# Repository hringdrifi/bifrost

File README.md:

# Bifrǫst

Bifrǫst is a split-keyboard design project by [hringdrifi](https://github.com/hringdrifi).

It is a wireless keyboard design based on the MDBT50Q module, which uses the Nordic nRF52840 SoC.

## Project status

This keyboard is currently under active design. It is not yet a validated or production-ready design.

The case CAD files and PCB design files are published here. The keyboard firmware is maintained in the [zmk-config-bifrost repository](https://github.com/hringdrifi/zmk-config-bifrost).

## Available files

- [`case/`](case/README.md) — STEP files for the cases and switch plates
- [`pcb/`](pcb/) — KiCad sources for the five PCBs
- [`docs/manufacturing.md`](docs/manufacturing.md) — manufacturing reference ([日本語](docs/manufacturing.ja.md))
- [Firmware](https://github.com/hringdrifi/zmk-config-bifrost) — ZMK configuration and firmware source

## License

The design data in `case/` and `pcb/` is licensed under the [CERN Open Hardware Licence Version 2 - Permissive (CERN-OHL-P-2.0)](LICENSE).

This license permits use, modification, manufacture, and sale of the design data and products made from it. Modified design data does not need to be published, but applicable notices must be retained and modifications must be documented. The design data and any resulting products are provided without warranty.

The CERN-OHL-P-2.0 license applies to the contents of `case/` and `pcb/`. Firmware is licensed under the [MIT License](https://spdx.org/licenses/MIT.html).

## Disclaimer

Verify dimensions, clearances, compatibility, manufacturability, and safety for your own build before making any parts. Use of these files is at your own risk.

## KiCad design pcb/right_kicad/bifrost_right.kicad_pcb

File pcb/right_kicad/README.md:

# Bifrǫst right KiCad design

KiCad source files for the right half of Bifrǫst.

## Status

This is an **incomplete and unverified work in progress**. Do not order boards or rely on this design without independently reviewing the schematic, layout, footprints, mechanical fit, and electrical connections.

The project was initially created from a Smiðr export, then received substantial additional modifications. It is no longer an unmodified Smiðr export.

## Contents

| Design | Purpose |
| --- | --- |
| `bifrost_right.kicad_pro` / `.kicad_sch` / `.kicad_pcb` | Right main PCB |
| `bifrost_right_plate.kicad_pro` / `.kicad_pcb` | Right main switch plate |
| `bifrost_right_thumb.kicad_pro` / `.kicad_sch` / `.kicad_pcb` | Right thumb-cluster PCB |
| `bifrost_right_thumb_plate.kicad_pro` / `.kicad_pcb` | Right thumb-cluster switch plate |
| `bifrost_right_trackball.kicad_pro` / `.kicad_sch` / `.kicad_pcb` | Trackball PCB |
| `smidr.pretty/` | Project footprint library |
| `local.kicad_sym` | Project symbol library |

## Electrical design note

The switch design uses **direct GPIO connections**. Each switch is connected directly between its assigned GPIO net and GND; **there is no diode connected to each switch**.

## Libraries

`fp-lib-table` and `sym-lib-table` configure the project libraries. Keep `smidr.pretty/` and `local.kicad_sym` with this project when opening it in KiCad.

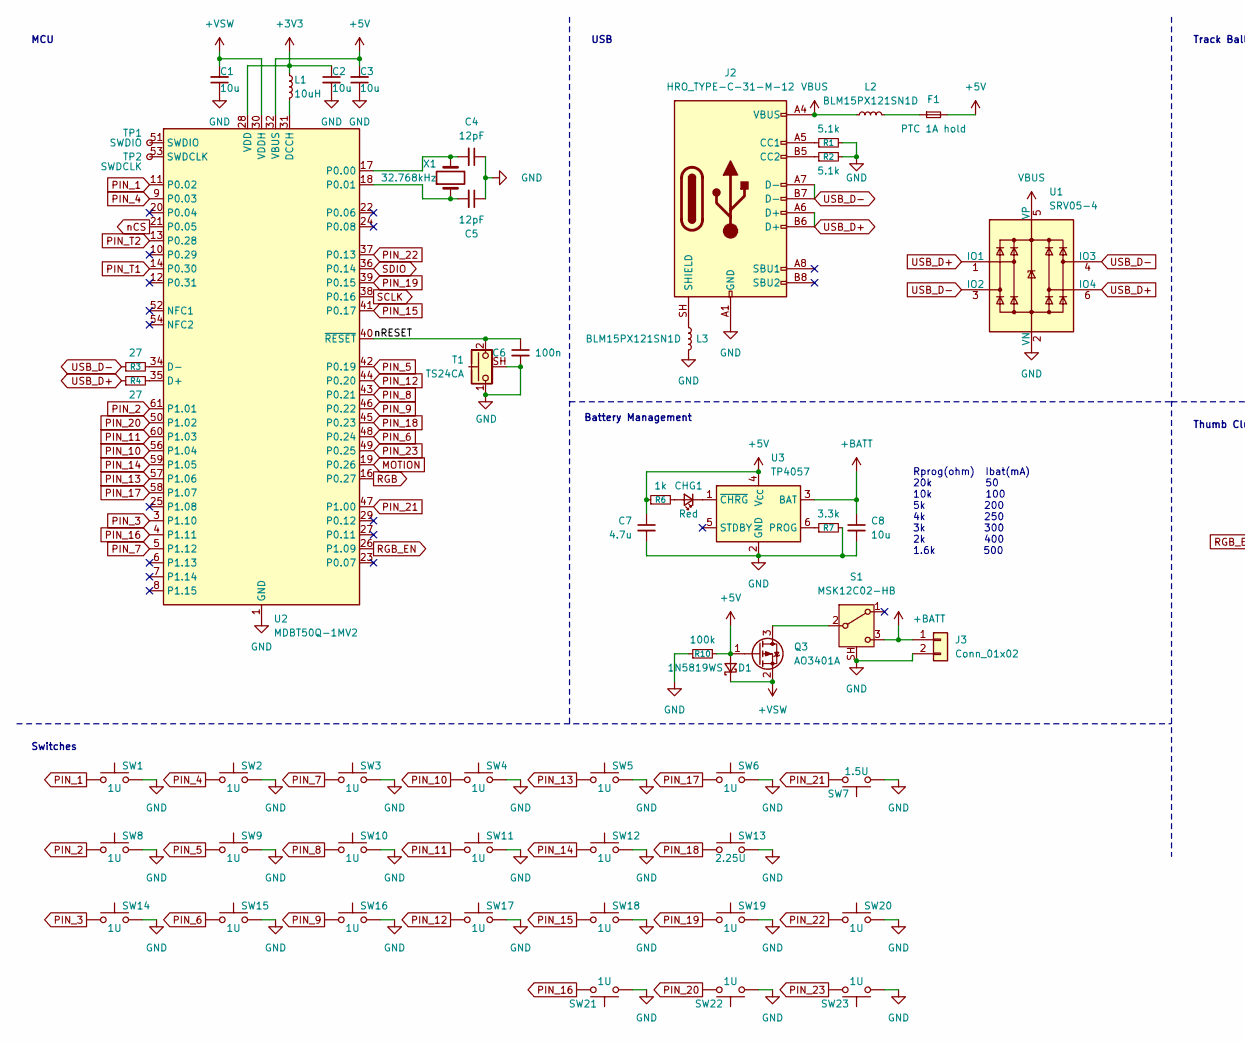
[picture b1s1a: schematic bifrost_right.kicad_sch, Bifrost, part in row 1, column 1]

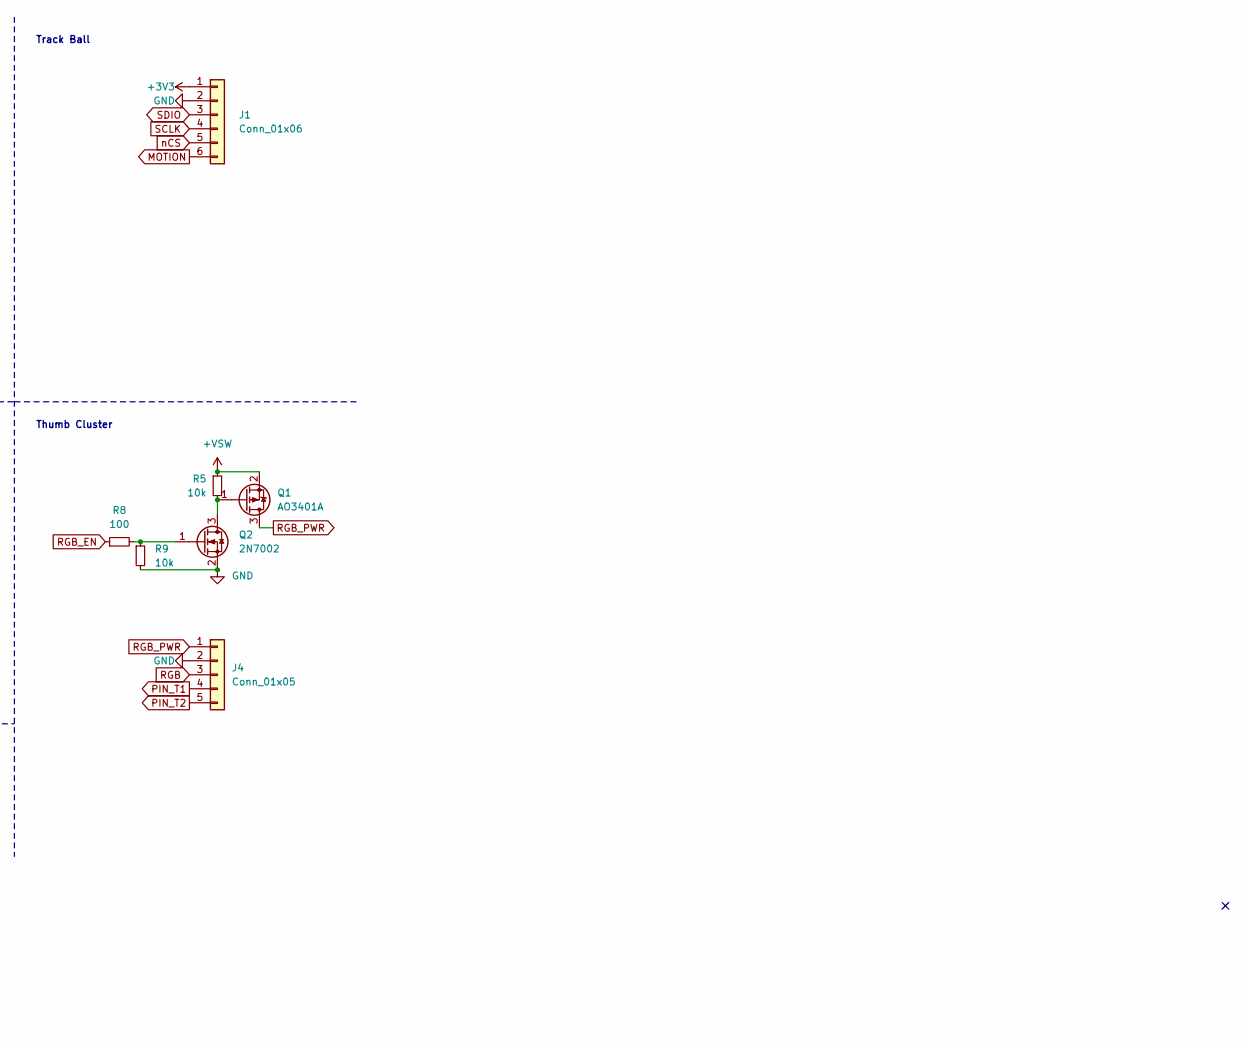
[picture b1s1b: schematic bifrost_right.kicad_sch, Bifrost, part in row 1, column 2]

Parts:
C1, C2, C3, C8: 10u; C_0402_1005Metric; JLCPCB Part # C15525
C4, C5: 12pF; C_0402_1005Metric; JLCPCB Part # C1547
C6: 100n; C_0402_1005Metric; JLCPCB Part # C1525
C7: 4.7u; C_0402_1005Metric; JLCPCB Part # C23733
CHG1: Red; LED_0603_1608Metric; JLCPCB Part # C19189741
D1: 1N5819WS; D_SOD-323; JLCPCB Part # C191023
F1: PTC 1A hold; Fuse_1206_3216Metric; JLCPCB Part # C883131
J1: Conn_01x06; PinHeader_1x06_P1.27mm_Vertical
J2: HRO_TYPE-C-31-M-12; USB_C_Receptacle_HRO_TYPE-C-31-M-12; JLCPCB Part # C165948
J3: Conn_01x02; PinHeader_1x02_P1.27mm_Vertical
J4: Conn_01x05; PinHeader_1x05_P1.27mm_Vertical
L1: 10uH; L_0603_1608Metric; JLCPCB Part # C86083
L2, L3: BLM15PX121SN1D; L_0402_1005Metric; JLCPCB Part # C88970
Q1, Q3: AO3401A; SOT-23; JLCPCB Part # C15127
Q2: 2N7002; SOT-23; JLCPCB Part # C8545
R1, R2: 5.1k; R_0402_1005Metric; JLCPCB Part # C25905
R3, R4: 27; R_0402_1005Metric; JLCPCB Part # C25100
R5, R9: 10k; R_0402_1005Metric; JLCPCB Part # C25744
R6: 1k; R_0402_1005Metric; JLCPCB Part # C11702
R7: 3.3k; R_0402_1005Metric; JLCPCB Part # C25890
R8: 100; R_0402_1005Metric; JLCPCB Part # C25076
R10: 100k; R_0402_1005Metric; JLCPCB Part # C25741
S1: MSK12C02-HB; SW_SPDT_Shouhan_MSK12C02; JLCPCB Part # C431541
SW1, SW2, SW3, SW4, SW5, SW6, SW8, SW9, SW10, SW11, SW12, SW14, SW15, SW16, SW17, SW18, SW19, SW20, SW21, SW22, SW23: 1U; SW_Smidr_Gateron_LP_Hotswap
SW7: 1.5U; SW_Smidr_Gateron_LP_Hotswap
SW13: 2.25U; SW_Smidr_Gateron_LP_Hotswap
T1: TS24CA; SW_SMD_2P-TS24CA; JLCPCB Part # C393942
TP1: SWDIO; TestPoint_THTPad_D1.0mm_Drill0.5mm
TP2: SWDCLK; TestPoint_THTPad_D1.0mm_Drill0.5mm
U1: SRV05-4; SOT-23-6; JLCPCB Part # C7420376
U2: MDBT50Q-1MV2; Raytac_MDBT50Q; JLCPCB Part # C5118826
U3: TP4057; SOT-23-6; JLCPCB Part # C12044
X1: 32.768kHz; Crystal_SMD_MicroCrystal_CC7V-T1A-2Pin_3.2x1.5mm; JLCPCB Part # C479190

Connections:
+3V3: C2.1, J1.1, L1.1, U2.28 (VDD)
+5V: C3.2, C7.1, D1.2 (A), F1.2, Q3.1 (G), R6.1, R10.2, U2.32 (VBUS), U3.4 (V_{CC})
+BATT: C8.1, J3.1, S1.3 (C), U3.3 (BAT)
+VSW: C1.2, D1.1 (K), Q1.2 (S), Q3.2 (S), R5.1, U2.30 (VDDH)
/nRESET: C6.1, T1.2, U2.40 (~RESET)
GND: C1.1, C2.2, C3.1, C4.1, C5.1, C6.2, C7.2, C8.2, J1.2, J2.A1 (GND), J2.A12 (GND), J2.B1 (GND), J2.B12 (GND), J3.2, J4.2, L3.2, Q2.2 (S), R1.2, R2.2, R7.2, R9.2, R10.1, S1.SH, SW1.2, SW2.2, SW3.2, SW4.2, SW5.2, SW6.2, SW7.1, SW8.2, SW9.2, SW10.2, SW11.2, SW12.2, SW13.2, SW14.2, SW15.2, SW16.2, SW17.2, SW18.2, SW19.2, SW20.2, SW21.1, SW22.1, SW23.1, T1.1, T1.SH (B), U1.2 (VN), U2.1 (GND), U2.2 (GND), U2.15 (GND), U2.33 (GND), U2.55 (GND), U3.2 (GND)
MOTION: J1.6, U2.19 (P0.26)
unnamed: CHG1.2 (A), R6.2
unnamed: CHG1.1 (K), U3.1 (~CHRG)
unnamed: F1.1, L2.2
unnamed: J2.A5 (CC1), R1.1
unnamed: J2.B5 (CC2), R2.1
unnamed: J2.SH (SHIELD), L3.1
unnamed: Q1.1 (G), Q2.3 (D), R5.2
unnamed: Q2.1 (G), R8.2, R9.1
unnamed: Q3.3 (D), S1.2 (B)
unnamed: R4.2, U2.35 (D+)
unnamed: R3.2, U2.34 (D-)
unnamed: L1.2, U2.31 (DCCH)
unnamed: C4.2, U2.17 (P0.00), X1.2
unnamed: C5.2, U2.18 (P0.01), X1.1
unnamed: TP2.1 (1_1), U2.53 (SWDCLK)
unnamed: TP1.1 (1_1), U2.51 (SWDIO)
unnamed: R7.1, U3.6 (PROG)
PIN_1: SW1.1, U2.11 (P0.02)
PIN_2: SW8.1, U2.61 (P1.01)
PIN_3: SW14.1, U2.3 (P1.10)
PIN_4: SW2.1, U2.9 (P0.03)
PIN_5: SW9.1, U2.42 (P0.19)
PIN_6: SW15.1, U2.48 (P0.24)
PIN_7: SW3.1, U2.5 (P1.12)
PIN_8: SW10.1, U2.43 (P0.21)
PIN_9: SW16.1, U2.46 (P0.22)
PIN_10: SW4.1, U2.56 (P1.04)
PIN_11: SW11.1, U2.60 (P1.03)
PIN_12: SW17.1, U2.44 (P0.20)
PIN_13: SW5.1, U2.57 (P1.06)
PIN_14: SW12.1, U2.59 (P1.05)
PIN_15: SW18.1, U2.41 (P0.17)
PIN_16: SW21.2, U2.4 (P1.11)
PIN_17: SW6.1, U2.58 (P1.07)
PIN_18: SW13.1, U2.45 (P0.23)
PIN_19: SW19.1, U2.39 (P0.15)
PIN_20: SW22.2, U2.50 (P1.02)
PIN_21: SW7.2, U2.47 (P1.00)
PIN_22: SW20.1, U2.37 (P0.13)
PIN_23: SW23.2, U2.49 (P0.25)
PIN_T1: J4.4, U2.14 (P0.30)
PIN_T2: J4.5, U2.13 (P0.28)
RGB: J4.3, U2.16 (P0.27)
RGB_EN: R8.1, U2.26 (P1.09)
RGB_PWR: J4.1, Q1.3 (D)
SCLK: J1.4, U2.38 (P0.16)
SDIO: J1.3, U2.36 (P0.14)
USB_D+: J2.A6 (D+), J2.B6 (D+), R4.1, U1.1 (IO1), U1.6 (IO4)
USB_D-: J2.A7 (D-), J2.B7 (D-), R3.1, U1.3 (IO2), U1.4 (IO3)
VBUS: J2.A4 (VBUS), J2.A9 (VBUS), J2.B4 (VBUS), J2.B9 (VBUS), L2.1, U1.5 (VP)
nCS: J1.5, U2.21 (P0.05)

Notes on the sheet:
Thumb Cluster
MCU
Battery Management
Track Ball
USB
Rprog(ohm) Ibat(mA) 20k 50 10k 100 5k 200 4k 250 3k 300 2k 400 1.6k 500
Switches

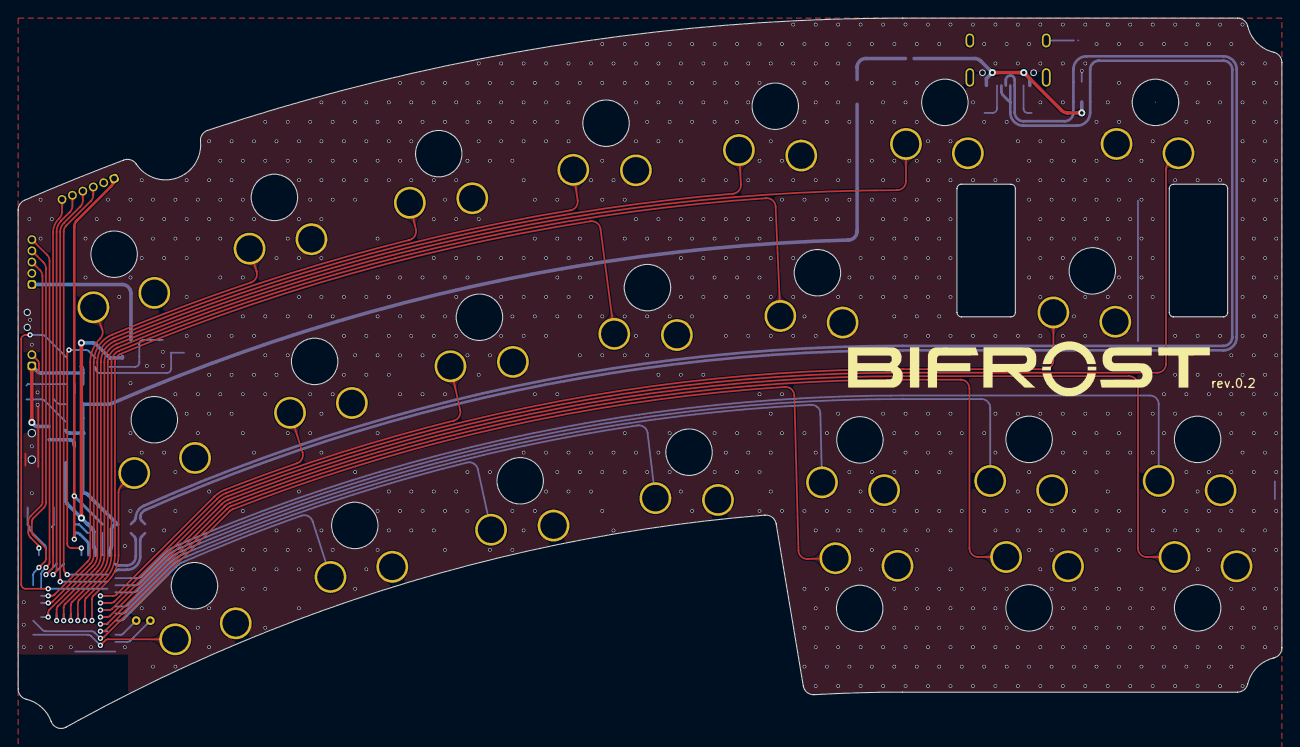
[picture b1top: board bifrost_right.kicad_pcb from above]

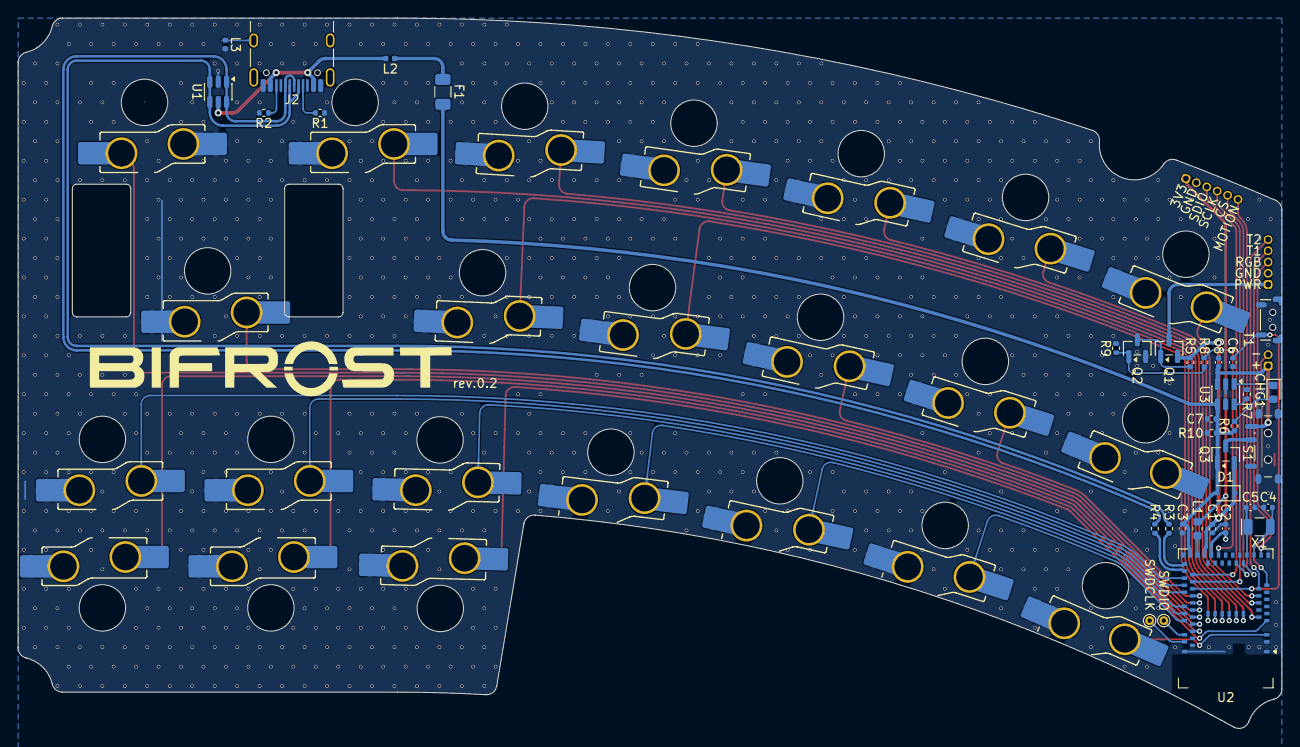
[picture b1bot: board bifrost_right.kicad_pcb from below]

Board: 2 copper layers, 142.9 x 80.3 mm, 62 parts (62 on the bottom side), 58 nets.

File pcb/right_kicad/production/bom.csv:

Designator,Footprint,Quantity,Value,LCSC Part #
"C1, C2, C3, C8",0402,4,10u,C15525
"C4, C5",0402,2,12pF,C1547
C6,0402,1,100n,C1525
C7,0402,1,4.7u,C23733
CHG1,0603,1,Red,C19189741
D1,D_SOD-323,1,1N5819WS,C191023
F1,1206,1,PTC 1A hold,C883131
J2,USB_C_Receptacle_HRO_TYPE-C-31-M-12,1,HRO_TYPE-C-31-M-12,C165948
L1,0603,1,10uH,C86083
"L2, L3",0402,2,BLM15PX121SN1D,C88970
"Q1, Q3",SOT-23,2,AO3401A,C15127
Q2,SOT-23,1,2N7002,C8545
"R1, R2",0402,2,5.1k,C25905
R10,0402,1,100k,C25741
"R3, R4",0402,2,27,C25100
"R5, R9",0402,2,10k,C25744
R6,0402,1,1k,C11702
R7,0402,1,3.3k,C25890
R8,0402,1,100,C25076
S1,SW_SPDT_Shouhan_MSK12C02,1,MSK12C02-HB,C431541
T1,SW_SMD_2P-TS24CA,1,TS24CA,C393942
TP1,TestPoint_THTPad_D1.0mm_Drill0.5mm,1,SWDIO,
TP2,TestPoint_THTPad_D1.0mm_Drill0.5mm,1,SWDCLK,
U1,SOT-23-6,1,SRV05-4,C7420376
U2,Raytac_MDBT50Q,1,MDBT50Q-1MV2,C5118826
U3,SOT-23-6,1,TP4057,C12044
X1,Crystal_SMD_MicroCrystal_CC7V-T1A-2Pin_3.2x1.5mm,1,32.768kHz,C479190

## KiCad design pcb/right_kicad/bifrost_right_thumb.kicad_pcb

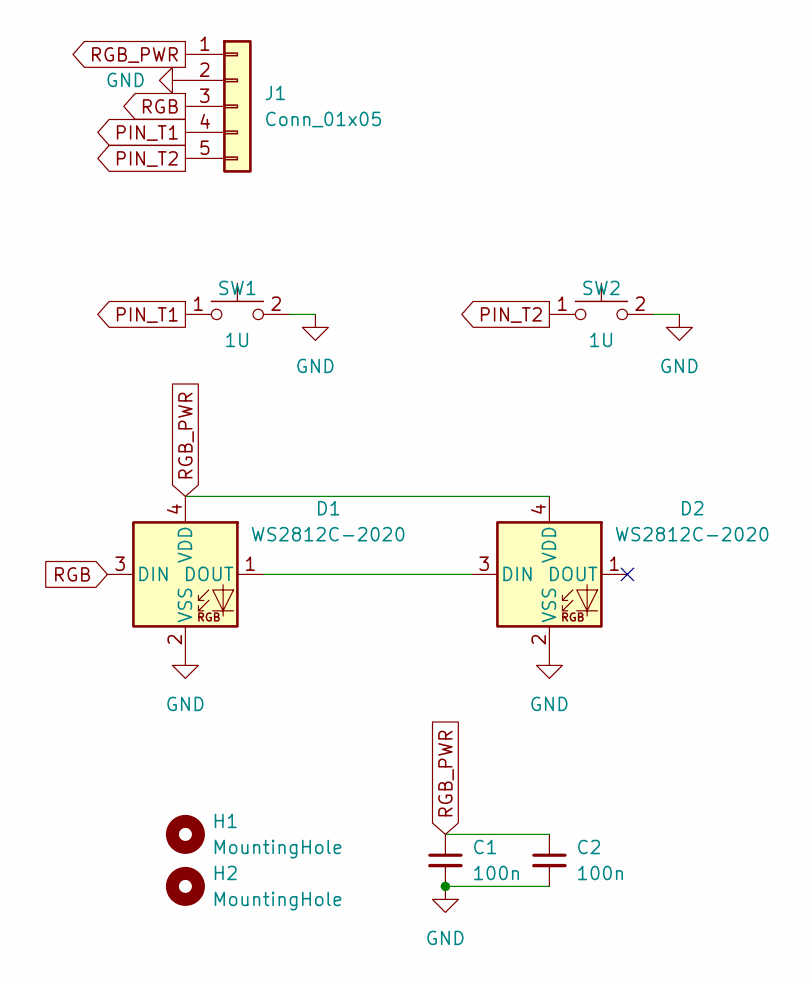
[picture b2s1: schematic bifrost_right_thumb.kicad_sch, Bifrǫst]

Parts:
C1, C2: 100n; C_0402_1005Metric; JLCPCB Part # C1525
D1, D2: WS2812C-2020; LED_WS2812B-2020_PLCC4_2.0x2.0mm; JLCPCB Part # C55109522
H1, H2: MountingHole; SMD-1_BD4.4-D2.8; JLCPCB Part # C2928179
J1: Conn_01x05; PinHeader_1x05_P1.27mm_Vertical
SW1, SW2: 1U; SW_Smidr_Gateron_LP_Hotswap

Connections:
GND: C1.2, C2.2, D1.2 (VSS), D2.2 (VSS), J1.2, SW1.2, SW2.2
unnamed: D1.1 (DOUT), D2.3 (DIN)
PIN_T1: J1.4, SW1.1
PIN_T2: J1.5, SW2.1
RGB: D1.3 (DIN), J1.3
RGB_PWR: C1.1, C2.1, D1.4 (VDD), D2.4 (VDD), J1.1

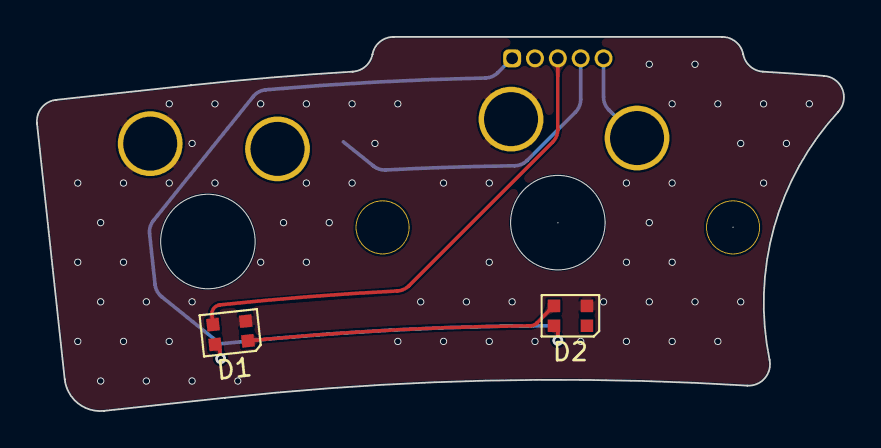
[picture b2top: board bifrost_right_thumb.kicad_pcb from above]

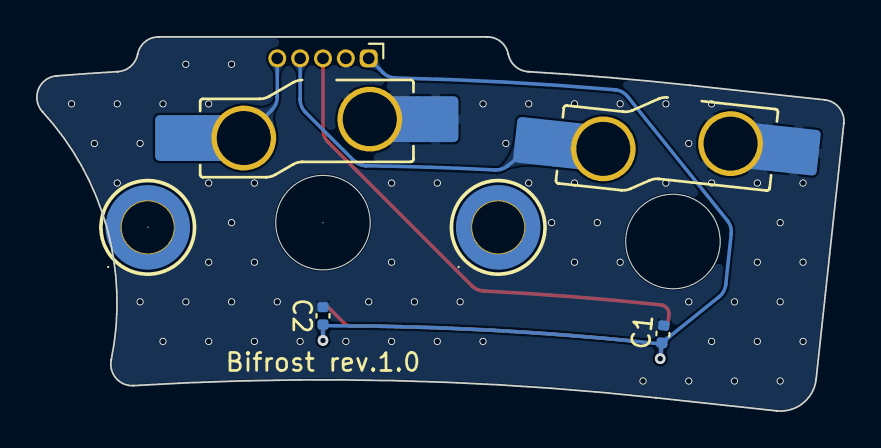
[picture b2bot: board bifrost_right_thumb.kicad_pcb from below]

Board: 2 copper layers, 44.8 x 20.8 mm, 9 parts (7 on the bottom side), 6 nets.

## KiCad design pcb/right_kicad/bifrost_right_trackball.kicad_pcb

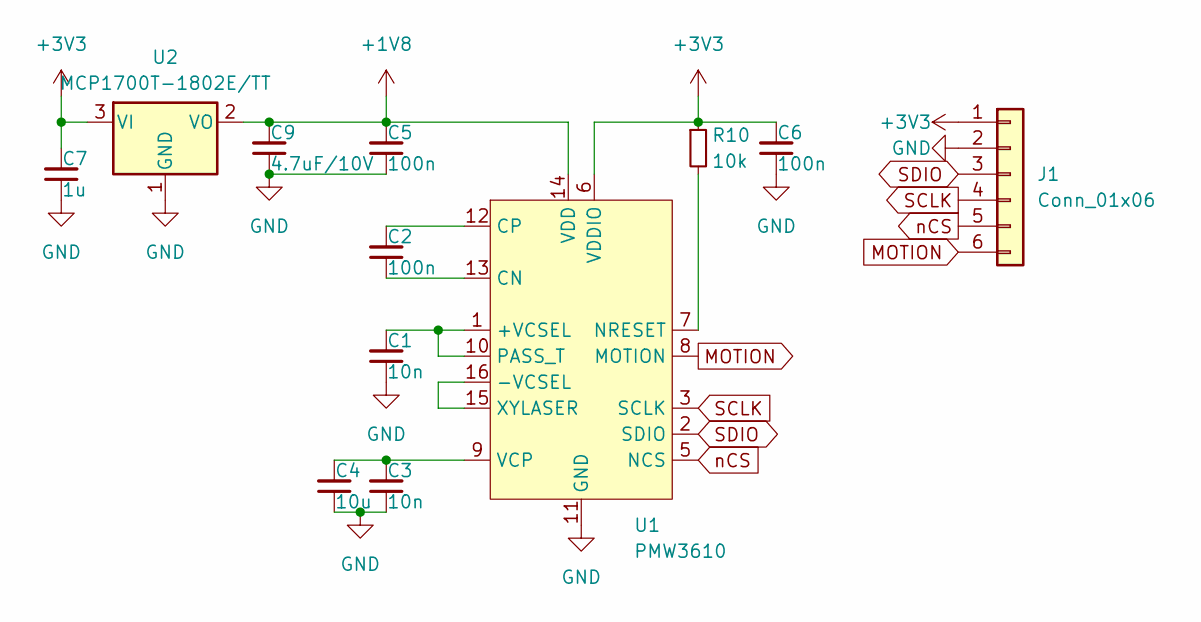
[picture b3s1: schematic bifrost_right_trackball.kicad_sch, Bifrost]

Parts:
C1, C3: 10n; C_0402_1005Metric; LCSC C15195
C2, C5, C6: 100n; C_0402_1005Metric; LCSC C1525
C4: 10u; C_0402_1005Metric; LCSC C15525
C7: 1u; C_0402_1005Metric; LCSC C52923
C9: 4.7uF/10V; C_0402_1005Metric; LCSC C23733
J1: Conn_01x06; PinHeader_1x06_P1.27mm_Vertical
R10: 10k; R_0402_1005Metric; LCSC C25744
U1: PMW3610; PMW3610DM-SUDU 16Pin; MFR. Part # PMW3610DM-SUDU; JLCPCB Part # C42442560
U2: MCP1700T-1802E/TT; SOT-23; LCSC C150796

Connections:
+1V8: C5.2, C9.2, U1.14 (VDD), U2.2 (VO)
+3V3: C6.2, C7.2, J1.1, R10.1, U1.6 (VDDIO), U2.3 (VI)
GND: C1.1, C3.1, C4.1, C5.1, C6.1, C7.1, C9.1, J1.2, U1.11 (GND), U2.1 (GND)
MOTION: J1.6, U1.8 (MOTION)
unnamed: C1.2, U1.1 (+VCSEL), U1.10 (PASS_T)
unnamed: U1.15 (XYLASER), U1.16 (-VCSEL)
unnamed: C2.1, U1.13 (CN)
unnamed: C2.2, U1.12 (CP)
unnamed: R10.2, U1.7 (NRESET)
unnamed: C3.2, C4.2, U1.9 (VCP)
SCLK: J1.4, U1.3 (SCLK)
SDIO: J1.3, U1.2 (SDIO)
nCS: J1.5, U1.5 (NCS)

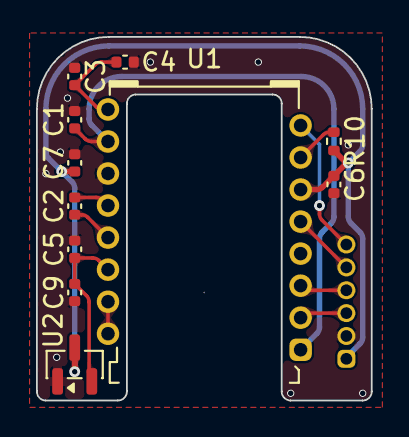
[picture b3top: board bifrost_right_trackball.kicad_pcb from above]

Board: 2 copper layers, 18.6 x 20.2 mm, 12 parts (1 on the bottom side), 13 nets.
